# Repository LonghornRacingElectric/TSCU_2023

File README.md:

# TSCU_2023

The Tractiv System Control Unit (TSCU) controls the main logic of the Tractiv system (contactors, IMD, etc).

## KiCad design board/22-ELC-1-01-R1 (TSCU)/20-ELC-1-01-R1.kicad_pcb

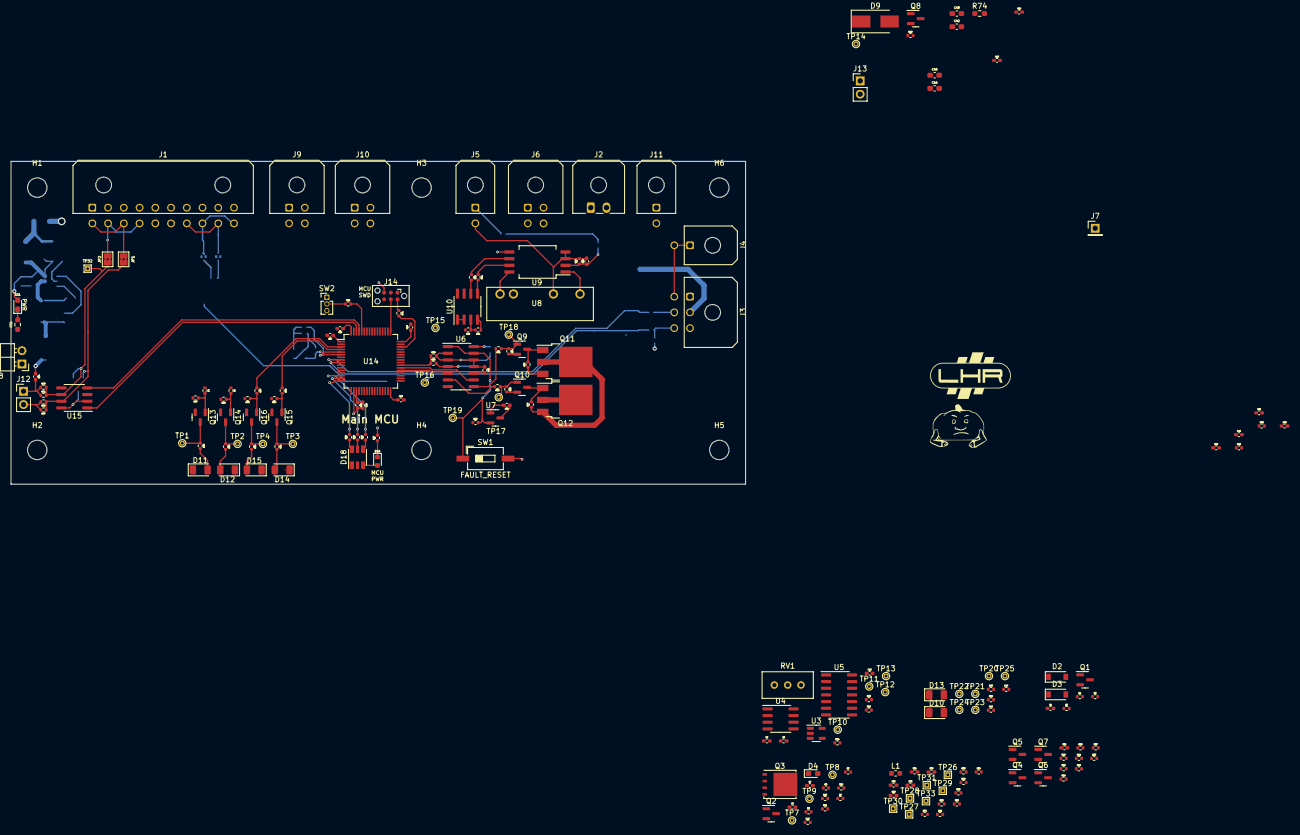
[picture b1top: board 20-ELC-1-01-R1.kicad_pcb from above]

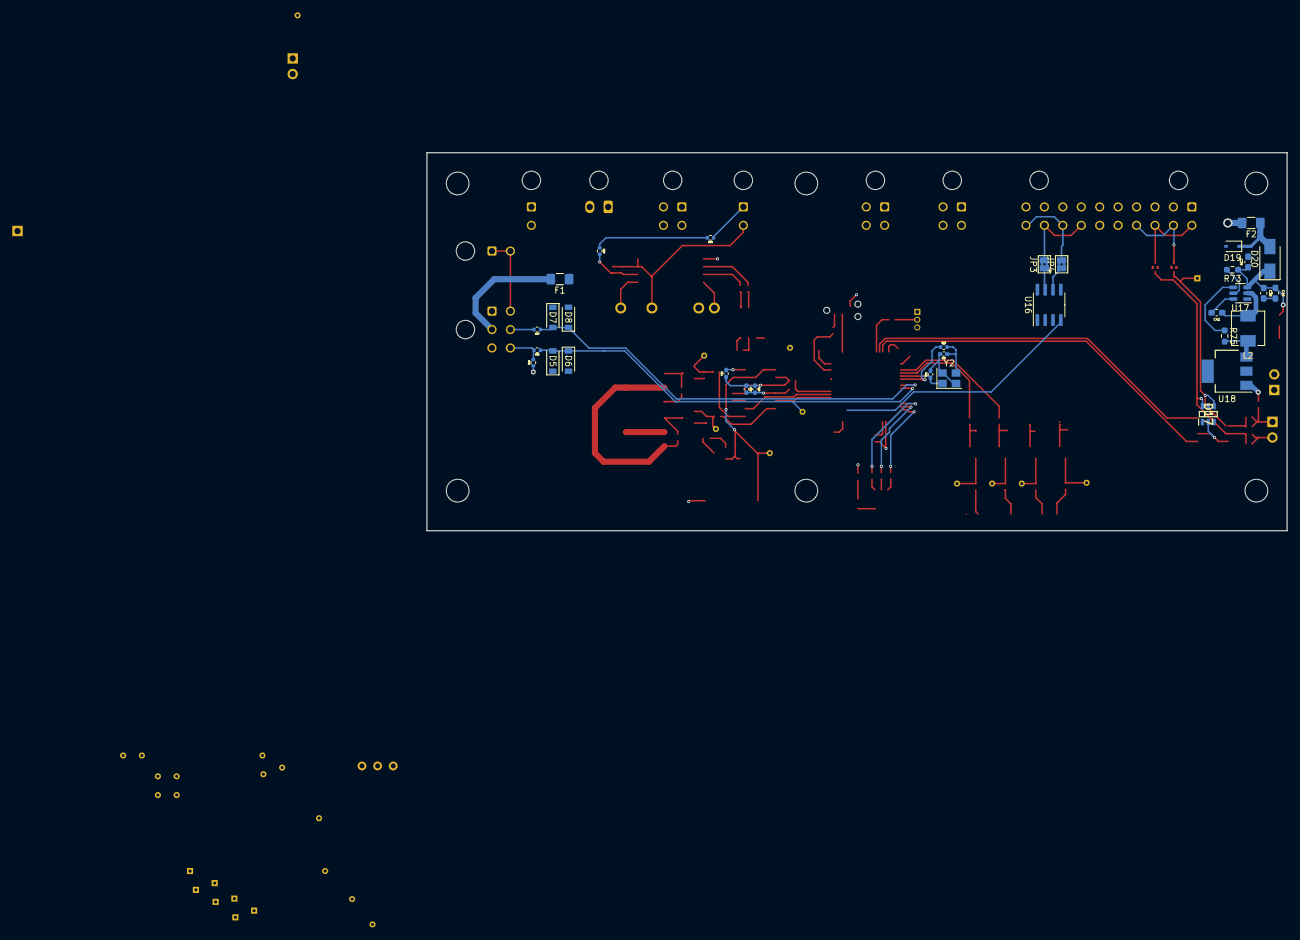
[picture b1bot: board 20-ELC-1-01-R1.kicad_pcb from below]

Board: 4 copper layers, 140.0 x 61.5 mm, 238 parts (33 on the bottom side), 130 nets.

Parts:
C1: 0.1uF; C_0402_1005Metric_Pad0.74x0.62mm_HandSolder_Reasonable_Text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
C6, C7, C9, C10, C11, C12, C13, C14, C15, C16, C17, C19, C20, C21, C22, C23: 0.1uf; C_0402_1005Metric_Pad0.74x0.62mm_HandSolder_Reasonable_Text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
C8: 47uf; C_0402_1005Metric_Pad0.74x0.62mm_HandSolder_Reasonable_Text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
C18: 1nf; C_0402_1005Metric_Pad0.74x0.62mm_HandSolder_Reasonable_Text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
C24: 4u7; C_0402_1005Metric_Pad0.74x0.62mm_HandSolder_Reasonable_Text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
C25, C26, C27, C28, C29: 100n; C_0402_1005Metric_Pad0.74x0.62mm_HandSolder_Reasonable_Text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
C30: 1u; C_0402_1005Metric_Pad0.74x0.62mm_HandSolder_Reasonable_Text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
C31: 10n; C_0402_1005Metric_Pad0.74x0.62mm_HandSolder_Reasonable_Text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
C32, C33: 0u1; C_0402_1005Metric_Pad0.74x0.62mm_HandSolder_Reasonable_Text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
C34, C35: 4.7n; C_0402_1005Metric_Pad0.74x0.62mm_HandSolder_Reasonable_Text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
C36, C37: 10p; C_0402_1005Metric_Pad0.74x0.62mm_HandSolder_Reasonable_Text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
C38, C39: 10uF; C_0603_1608Metric_Pad1.08x0.95mm_HandSolder_Reasonable_Text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
C40, C41: 100nF; C_0603_1608Metric_Pad1.08x0.95mm_HandSolder_Reasonable_Text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
C42, C43, C45: 22uF; C_0603_1608Metric_Pad1.08x0.95mm_HandSolder_Reasonable_Text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
C44: 1uF; C_0603_1608Metric_Pad1.08x0.95mm_HandSolder_Reasonable_Text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
D2, D3, D5, D6, D7, D8: B5819W; D_SOD-123
D4: LED_RED; LED_0603_1608Metric_Pad1.05x0.95mm_HandSolder
D9: P6SMB16CA; D_SMB_Handsoldering
D10: AMS_LED; LED_1206_3216Metric
D11: BMS_FAULT_LED; LED_1206_3216Metric
D12: IMS_FAULT_LED; LED_1206_3216Metric
D13: IMS_LED; LED_1206_3216Metric
D14: Precharge_CMD_LED; LED_1206_3216Metric
D15: Final_Close_Out_LED; LED_1206_3216Metric
D16: RED; LED_0603_1608Metric
D17: DT1446-04TS-7; SOT95P280X100-6N
D18: SMLVN6RGB; LED_ROHM_SMLVN6
D19: 32V; D_SOD-323
D20: 0.7dV; D_SMA
D21: LED; LED_0603_1608Metric_Pad1.05x0.95mm_HandSolder
F1, F2: 2A; Fuse_1206_3216Metric_Pad1.42x1.75mm_HandSolder
H1, H2, H3, H4, H5, H6: MountingHole; MountingHole_3.7mm
J1: Conn_01x20; Molex_Micro-Fit_3.0_43045-2000_2x10_P3.00mm_Horizontal
J2: Conn_01x02_Female; Molex_Micro-Fit_3.0_43650-0200_1x02_P3.00mm_Horizontal
J3: Conn_01x06; Molex_Micro-Fit_3.0_43045-0600_2x03_P3.00mm_Horizontal
J4, J5: Conn_01x02; Molex_Micro-Fit_3.0_43045-0200_2x01_P3.00mm_Horizontal
J6: Conn_01x06; Molex_Micro-Fit_3.0_43045-0400_2x02_P3.00mm_Horizontal
J7: Conn_01x01; PinHeader_1x01_P2.54mm_Vertical
J8: Conn_01x02; PinHeader_1x02_P2.54mm_Horizontal
J9, J10: Conn_02x02_Counter_Clockwise; Molex_Micro-Fit_3.0_43045-0400_2x02_P3.00mm_Horizontal
J11: Conn_01x01; Molex_Micro-Fit_3.0_43045-0200_2x01_P3.00mm_Horizontal
J12, J13: Conn_01x02; PinHeader_1x02_P2.54mm_Vertical
J14: SWD; Tag-Connect_TC2030-IDC-NL_2x03_P1.27mm_Vertical
JP1, JP2, JP3, JP4: SolderJumper-2_P1.3mm_Bridged2Bar_Pad1.0x1.5mm
L1: 68n; L_0603_1608Metric
L2: 4u7; L_Sunlord_MWSA0518_5.4x5.2mm
Q1, Q4, Q5, Q6, Q7, Q9, Q10, Q13, Q14, Q15, Q16: AO3400A; SOT-23
Q2: 2N7002; SOT-23
Q3: CSD18540Q5B; TDSON-8-1
Q8: Q_NMOS_DGS; SOT-23
Q11, Q12: SUD50P04-09L-E3; TO-252-3_TabPin2
R1, R3, R25, R29, R41, R42: 2.2k; R_0402_1005Metric
R2, R4, R5, R6, R8, R18, R19, R20, R26, R28, R30, R33, R76, R77: 10k; R_0402_1005Metric
R7, R57: 100; R_0402_1005Metric
R9, R13, R17, R27, R31, R32, R40: 1k; R_0402_1005Metric
R10, R11: 5.1k; R_0402_1005Metric
R12, R38, R39: 1M; R_0402_1005Metric
R14, R16, R21, R22, R23, R24, R34, R35, R36, R37, R47#2, R48#2, R78, R79: 100k; R_0402_1005Metric
R15: 120k; R_0402_1005Metric
R43, R44: 500; R_0402_1005Metric
R45, R46: 3.9k; R_0402_1005Metric
R47, R48, R49, R49#2, R50, R50#2, R51, R52, R58, R59, R60: 220; R_0402_1005Metric
R53, R54, R55, R56: 2k2; R_0402_1005Metric
R61, R62, R63, R64, R65, R66, R67, R68: 120; R_0402_1005Metric
R69: 47; R_0402_1005Metric
R70: 10K; R_0402_1005Metric
R71: 22; R_0402_1005Metric
R72: 470R; R_0603_1608Metric_Pad0.98x0.95mm_HandSolder
R73, R74: 10K; R_0603_1608Metric_Pad0.98x0.95mm_HandSolder
R75: 54.9K; R_0603_1608Metric_Pad0.98x0.95mm_HandSolder
RV1: R_POT_TRIM; Potentiometer_Bourns_3296W_Vertical
SW1: FAULT_RESET; SW_DIP_SPSTx01_Slide_6.7x4.1mm_W8.61mm_P2.54mm_LowProfile
SW2: SW_SPDT; PinHeader_1x03_P1.27mm_Vertical
TP1, TP2, TP3, TP4, TP7, TP8, TP9, TP10, TP11, TP12, TP13, TP14, TP15, TP16, TP17, TP18, TP19, TP20, TP21, TP22, TP23, TP24, TP25: TestPoint; TestPoint_THTPad_D1.0mm_Drill0.5mm
TP26, TP27, TP28, TP29, TP30, TP31, TP32, TP33: TestPoint_THTPad_1.0x1.0mm_Drill0.5mm
U3: 74AUC1G17; SOT-23-5
U4: LM393; SOIC-8_3.9x4.9mm_P1.27mm
U5: 74HC08_2AND; SOIC-14_3.9x8.7mm_P1.27mm
U6: 74HC74D,653; SOIC-14_3.9x8.7mm_P1.27mm
U7: SGM809-SXN3/TR; SOT-23
U8: RFMM-0505S
U9: ACPL-C79B; SSO-8_6.8x5.9mm_P1.27mm_Clearance8mm
U10: LM358; SOIC-8_3.9x4.9mm_P1.27mm
U14: STM32F105RCTx; LQFP-64_10x10mm_P0.5mm
U15, U16: SN65HVD230; SOIC-8_3.9x4.9mm_P1.27mm
U17: LMR51420; SOT-23-6
U18: AMS1117-3.3; SOT-223-3_TabPin2
X1: placeholder_for_picture; g_noidontwantthat
X2: placeholder_for_picture; logo_lhr
Y2: 16MHz; Crystal_SMD_3225-4Pin_3.2x2.5mm

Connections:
+3.3VA: C30.1, C31.1, L1.2, U14.13 (VDDA)
+3V3: C17.1, C24.1, C25.1, C26.1, C27.1, C28.1, C29.1, C32.1, C33.1, C45.1, D16.2 (A), D18.1 (BA), D18.2 (RA), D18.3 (GA), J14.1, L1.1, R53.1, R54.1, R55.1, R56.1, SW2.1 (A), U7.3 (VCC), U14.1 (VBAT), U14.19 (VDD), U14.32 (VDD), U14.48 (VDD), U14.64 (VDD), U15.3 (VCC), U16.3 (VCC), U18.2 (VO)
+5V: C6.2, C7.2, C9.1, C10.1, C14.2, C20.2, C23.1, C42.1, C43.1, C44.1, D2.1 (K), D5.1 (K), D7.1 (K), D17.5 (VCC), J8.1, L2.2, R1.1, R2.1, R8.1, R10.2, R11.2, R16.1, R33.1, R43.1, R75.2, RV1.1, U3.5 (VCC), U4.8 (V+), U5.14 (Vcc), U6.14 (VCC), U8.1 (VIN+), U9.8 (VDD2), U10.8 (V+), U18.3 (VI)
+24V: F1.1, F2.2, J1.2
/AMS_led: J1.8, Q4.3 (D)
/A_Vcar_sig: C21.1, R45.1, U10.7, U14.25 (PC5)
/BMS_Fault: R29.1, R30.1, TP15.1, U14.39 (PC8)
/BMS_fault_analog: C1.1, D2.2 (A), D3.1 (K), R3.1, U14.10 (PC2)
/CAN_H: J1.11, J1.13, JP1.2 (B)
/CAN_L: J1.12, J1.14, JP2.2 (B)
/Contactor Logic/Precharge_Active: R14.1, R15.1, TP10.1, U5.3 (1Y)
/D_AMS_Fault_Latched: R4.1, R18.1, U6.5 (Q), U14.37 (PC6)
/D_Aux_HS_sig: C7.1, J10.2, R11.1, TP8.1, U14.11 (PC3)
/D_Aux_LS_sig: C6.1, J9.2, R10.1, TP9.1, U5.2 (1B), U14.24 (PC4)
/D_Final_Close_Out: R13.1, R77.1, U5.6 (2Y), U14.3 (PC14)
/D_IMD_Fault_Latched: R5.1, R19.2, U6.9 (Q), U14.38 (PC7)
/D_Precharge_cmd: R28.2, R76.1, U5.1 (1A), U14.4 (PC15)
/D_Shutdown_Status_sig: R7.1, R8.2, R9.1, U14.40 (PC9)
/GLV Connections/DCDC_enable: J1.15, Q6.3 (D)
/HS_Con_GND: J6.2, Q3.1 (S), Q3.2 (S), Q3.3 (S), R12.2
/IMD_24V: F1.2, J3.2
/IMD_KE: J3.3, J3.4, J4.1, J4.2
/IMD_data: D7.2 (A), D8.1 (K), R27.1, U14.8 (PC0)
/IMD_data_low_side: J3.5, R27.2
/IMD_fault: C12.2, C15.2, D5.2 (A), D6.1 (K), R26.1, TP16.1, U6.10 (~S), U14.9 (PC1)
/IMD_led: J1.7, Q5.3 (D)
/IMD_status_output: J1.16, J3.6, R25.2, R26.2
/LS_Con_GND: J6.3, J9.3
/Microcontroller/BOOT0: R70.2, U14.60 (BOOT0)
/Microcontroller/CAN1_RX: TP28.1, U14.61 (PB8), U15.4 (R)
/Microcontroller/CAN1_TX: TP26.1, U14.62 (PB9), U15.1 (D)
/Microcontroller/CAN2_RX: TP29.1, U14.33 (PB12), U16.4 (R)
/Microcontroller/CAN2_TX: TP27.1, U14.34 (PB13), U16.1 (D)
/Microcontroller/HSE_in: C36.1, U14.5 (PD0), Y2.1
/Microcontroller/HSE_out: R69.1, U14.6 (PD1)
/Microcontroller/I2C1_SCL: R53.2, U14.58 (PB6)
/Microcontroller/I2C1_SDA: R54.2, U14.59 (PB7)
/Microcontroller/I2C2_SCL: R55.2, U14.29 (PB10)
/Microcontroller/I2C2_SDA: R56.2, U14.30 (PB11)
/Microcontroller/LED_B: R58.2, U14.16 (PA2)
/Microcontroller/LED_G: R59.2, U14.15 (PA1)
/Microcontroller/LED_R: R60.2, U14.14 (PA0)
/Microcontroller/SWCLK: J14.4, U14.49 (PA14)
/Microcontroller/SWDIO: R71.2, U14.46 (PA13)
/Orion_mpo_data_error: J2.2, Q1.1 (G), R1.2
/Power Supply 1/BUCK/EN: R73.2, U17.5 (EN)
/Power Supply 1/BUCK/SW: C41.1, L2.1, U17.2 (SW)
/Power Supply 1/BUCK/VBST: C41.2, U17.6 (VBST)
/Power Supply 1/BUCK/VFB: R74.1, R75.1, U17.4 (VFB)
/Power Supply 1/BUCK/V_in: C38.1, C39.1, C40.1, D20.1 (K), D21.2 (A), R73.1, U17.3 (VIN)
/Power Supply 1/DIODE: D19.1 (K), D20.2 (A), F2.1
/Precharge_Con_GND: J6.1, Q8.2 (S)
/Precharge_Timer: C8.1, R15.2, TP11.1, U3.2
/Shutdown Circuit Control/latch_ready: R33.2, SW1.1, TP19.1, U6.1 (~R), U6.13 (~R), U7.2 (~RESET)
/Telemetry_CAN_H: J1.17, J1.19, JP3.2 (B)
/Telemetry_CAN_L: J1.18, J1.20, JP4.2 (B)
/Voltage Measurement/HV+: J5.1, R38.1
/Voltage Measurement/iso_hv_0: C18.2, C19.1, J5.2, R40.2, U8.5 (VOUT-), U9.3 (IN-), U9.4 (GND1)
/Voltage Measurement/iso_hv_5: C19.2, U8.7 (VOUT+), U9.1 (VDD1)
/dcdc_enable: R20.2, U14.2 (PC13)
/shutdown_contactor: D9.1 (A1), J1.5, J9.4, J10.4, J11.1, R6.1, R17.2, TP7.1
/shutdown_in: J1.3, Q11.3 (S), R36.1
/shutdown_out: J1.4, Q12.2 (D)
/~dischage_disable: J1.6, Q7.3 (D)
GND: C1.2, C8.2, C9.2, C10.2, C11.2, C12.1, C13.1, C14.1, C15.1, C16.1, C17.2, C20.1, C22.1, C23.2, C24.2, C25.2, C26.2, C27.2, C28.2, C29.2, C30.2, C31.2, C32.2, C33.2, C34.1, C35.1, C36.2, C37.2, C38.2, C39.2, C40.2, C42.2, C43.2, C44.2, C45.2, D3.2 (A), D4.1 (K), D6.2 (A), D8.2 (A), D10.1 (K), D11.1 (K), D12.1 (K), D13.1 (K), D14.1 (K), D15.1 (K), D17.2 (VSS), D19.2 (A), J1.1, J2.1, J3.1, J7.1, J8.2, J9.1, J10.1, J14.5, Q1.2 (S), Q2.2 (S), Q4.2 (S), Q5.2 (S), Q6.2 (S), Q7.2 (S), Q9.2 (S), Q10.2 (S), Q13.2 (S), Q14.2 (S), Q15.2 (S), Q16.2 (S), R14.2, R21.2, R22.2, R23.2, R24.2, R25.1, R29.2, R34.2, R35.2, R44.2, R46.1, R47#2.2, R48#2.2, R57.2, R72.1, R74.2, R78.2, R79.2, RV1.3, SW1.2, SW2.3 (C), U3.3 (GND), U4.4 (V-), U5.7 (GND), U5.9 (3A), U5.10 (3B), U5.12 (4A), U5.13 (4B), U6.2 (D), U6.3 (C), U6.7 (GND), U6.11 (C), U6.12 (D), U7.1 (GND), U8.2 (VIN-), U9.5 (GND2), U10.4 (V-), U14.12 (VSSA), U14.18 (VSS), U14.31 (VSS), U14.47 (VSS), U14.63 (VSS), U15.2 (GND), U15.8 (Rs), U16.2 (GND), U16.8 (Rs), U17.1 (GND), U18.1 (GND), Y2.2, Y2.4
unnamed: C11.1, Q7.1 (G), R17.1, R24.1
unnamed: C13.2, C16.2, R30.2, U6.4 (~S)
unnamed: C18.1, R39.2, R40.1, U9.2 (IN+)
unnamed: C21.2, R42.2, R45.2, U10.6 (-)
unnamed: C22.2, R41.2, R46.2, U10.5 (+)
unnamed: C34.2, J12.1, R61.1, R63.1
unnamed: C35.2, J13.1, R62.1, R64.1
unnamed: C37.1, R69.2, Y2.3
unnamed: D4.2 (A), R9.2
unnamed: D9.2 (A2), J11.2, Q8.3 (D)
unnamed: D10.2 (A), R47.2
unnamed: D11.2 (A), R48.2, R49.2
unnamed: D12.2 (A), R49#2.2, R50.2
unnamed: D13.2 (A), R50#2.2
unnamed: D14.2 (A), R51.2
unnamed: D15.2 (A), R52.2
unnamed: D16.1 (K), R57.1
unnamed: D17.1 (I/O1), JP4.1 (A), R62.2, R64.2, TP33.1, U16.6 (CANL)
unnamed: D17.3 (I/O2), JP3.1 (A), R66.1, R68.1, TP31.1, U16.7 (CANH)
unnamed: D17.4 (I/O3), JP2.1 (A), R61.2, R63.2, TP32.1, U15.6 (CANL)
unnamed: D17.6 (I/O4), JP1.1 (A), R65.1, R67.1, TP30.1, U15.7 (CANH)
unnamed: D18.4 (GK), R60.1
unnamed: D18.5 (RK), R59.1
unnamed: D18.6 (BK), R58.1
unnamed: D21.1 (K), R72.2
unnamed: J10.3, Q3.5 (D)
unnamed: J12.2, R65.2, R67.2
unnamed: J13.2, R66.2, R68.2
unnamed: J14.2, R71.1
unnamed: Q1.3 (D), R2.2, R3.2
unnamed: Q2.1 (G), R6.2
unnamed: Q2.3 (D), R7.2
unnamed: Q3.4 (G), R12.1, R13.2
unnamed: Q4.1 (G), R18.2, R21.1
unnamed: Q5.1 (G), R19.1, R22.1
unnamed: Q6.1 (G), R20.1, R23.1
unnamed: Q8.1 (G), R28.1, TP14.1
unnamed: Q9.1 (G), R31.1, R34.1, TP18.1
unnamed: Q10.1 (G), R32.1, R35.1, TP17.1
unnamed: Q10.3 (D), Q12.1 (G), R37.2
unnamed: Q9.3 (D), Q11.1 (G), R36.2
unnamed: Q11.2 (D), Q12.3 (S), R37.1
unnamed: Q13.1 (G), R4.2, R47#2.1
unnamed: Q13.3 (D), R49.1, TP1.1
unnamed: Q14.1 (G), R5.2, R48#2.1
unnamed: Q14.3 (D), R50.1, TP2.1
unnamed: Q15.1 (G), R76.2, R78.1
unnamed: Q16.1 (G), R77.2, R79.1
unnamed: R16.2, TP13.1, U4.1, U5.4 (2A)
unnamed: R31.2, U6.8 (~Q)
unnamed: R32.2, U6.6 (~Q)
unnamed: R38.2, R39.1
unnamed: R41.1, U9.7 (OUT+)
unnamed: R42.1, U9.6 (OUT-)
unnamed: R43.2, R44.1, U10.3 (+)
unnamed: R47.1, TP20.1
unnamed: R48.1, TP21.1
unnamed: R49#2.1, TP22.1
unnamed: R50#2.1, TP23.1
unnamed: Q15.3 (D), R51.1, TP3.1, TP24.1
unnamed: Q16.3 (D), R52.1, TP4.1, TP25.1
unnamed: R70.1, SW2.2 (B)
unnamed: RV1.2, U4.2 (-)
unnamed: TP12.1, U3.4, U4.3 (+)
unnamed: U10.1, U10.2 (-)

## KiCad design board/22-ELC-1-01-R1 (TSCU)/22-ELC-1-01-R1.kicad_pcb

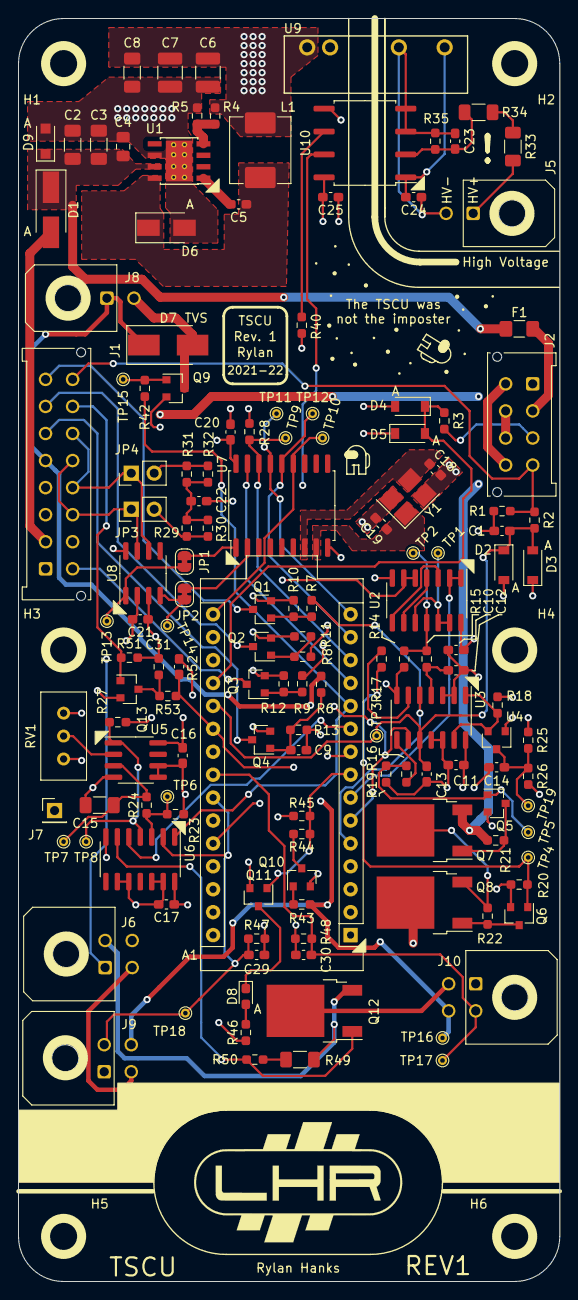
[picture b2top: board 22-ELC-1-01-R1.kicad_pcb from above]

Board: 4 copper layers, 60.0 x 140.0 mm, 150 parts (0 on the bottom side), 90 nets.

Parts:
A1: Arduino_Nano_v3.x; Arduino_Nano_Every
C1, C9, C10, C11, C12, C13, C14, C16, C17, C20, C21, C24, C25, C29, C30: 0.1uf; C_0603_1608Metric_Pad1.08x0.95mm_HandSolder
C2, C3, C8: 22uF; C_1206_3216Metric_Pad1.33x1.80mm_HandSolder
C4: 10uF; C_0805_2012Metric_Pad1.18x1.45mm_HandSolder
C5: 10nF; C_0603_1608Metric_Pad1.08x0.95mm_HandSolder
C6, C7: 100uF; C_1210_3225Metric_Pad1.33x2.70mm_HandSolder
C15: 68uf; C_1206_3216Metric_Pad1.33x1.80mm_HandSolder
C18, C19: 22pf; C_0603_1608Metric_Pad1.08x0.95mm_HandSolder
C22: 4.7nF; C_0603_1608Metric_Pad1.08x0.95mm_HandSolder
C23: 1nf; C_0603_1608Metric_Pad1.08x0.95mm_HandSolder
C31: 0.1uF; C_0603_1608Metric_Pad1.08x0.95mm_HandSolder
D1: SS54; D_SMA_Handsoldering
D2, D3, D4, D5: B5819W; D_SOD-123
D6: SS34; D_SMA
D7: P6SMB16CA; D_SMB_Handsoldering
D8: KT-0603R; LED_0603_1608Metric_Pad1.05x0.95mm_HandSolder
D9: D_SOD-123F
F1: 2A; Fuse_1206_3216Metric_Pad1.42x1.75mm_HandSolder
H1, H2, H3, H4, H5, H6: MountingHole; MountingHole_3.7mm
J1: Conn_01x116; Molex_Micro-Fit_3.0_43045-1612_2x08_P3.00mm_Vertical
J2: Conn_01x08; Molex_Micro-Fit_3.0_43045-0812_2x04_P3.00mm_Vertical
J5: Conn_01x02; Molex_Micro-Fit_3.0_43045-0200_2x01_P3.00mm_Horizontal
J6: Conn_01x06; Molex_Micro-Fit_3.0_43045-0400_2x02_P3.00mm_Horizontal
J7: Conn_01x01; PinHeader_1x01_P2.54mm_Vertical
J8: Conn_01x01; Molex_Micro-Fit_3.0_43045-0200_2x01_P3.00mm_Horizontal
J9, J10: Conn_02x02_Counter_Clockwise; Molex_Micro-Fit_3.0_43045-0400_2x02_P3.00mm_Horizontal
JP1, JP2: Jumper_2_Bridged; SolderJumper-2_P1.3mm_Bridged_RoundedPad1.0x1.5mm
JP3, JP4: NO_Jumper; PinHeader_1x02_P2.54mm_Vertical
L1: 15uH (4.5A); L_Abracon_ASPI-0630LR
Q1, Q2, Q3, Q4, Q5, Q6, Q11, Q13: AO3400A; SOT-23
Q7, Q8: IRFR5305TRPBF; TO-252-2
Q9: Q_NMOS_DGS; SOT-23
Q10: 2N7002; SOT-23
Q12: NCE3050K; TO-252-2
R1, R14, R51, R53: 2.2k; R_0603_1608Metric_Pad0.98x0.95mm_HandSolder
R2, R4, R7, R8, R9, R15, R18, R25, R42, R43, R45, R52: 10k; R_0603_1608Metric_Pad0.98x0.95mm_HandSolder
R3, R6, R16, R17, R35, R46, R50: 1k; R_0603_1608Metric_Pad0.98x0.95mm_HandSolder
R5: 3.24k; R_0603_1608Metric_Pad0.98x0.95mm_HandSolder
R10, R11, R12, R13, R19, R20, R21, R22, R23, R24, R27, R28: 100k; R_0603_1608Metric_Pad0.98x0.95mm_HandSolder
R26: 20k; R_0603_1608Metric_Pad0.98x0.95mm_HandSolder
R29, R30, R31, R32: 120; R_0603_1608Metric_Pad0.98x0.95mm_HandSolder
R33, R34, R49: 1M; R_1206_3216Metric_Pad1.30x1.75mm_HandSolder
R40: 3.9k; R_0603_1608Metric_Pad0.98x0.95mm_HandSolder
R44: 150; R_0603_1608Metric_Pad0.98x0.95mm_HandSolder
R47, R48: 5.1k; R_0603_1608Metric_Pad0.98x0.95mm_HandSolder
RV1: R_POT_TRIM; Potentiometer_Bourns_3296W_Vertical
TP1, TP2, TP3, TP4, TP5, TP6, TP7, TP8, TP9, TP10, TP11, TP12, TP13, TP14, TP15, TP16, TP17, TP18, TP19: TestPoint; TestPoint_THTPad_D1.0mm_Drill0.5mm
U1: TPS5430DDA; TI_SO-PowerPAD-8_ThermalVias
U2: 74HC00D,653; SOIC-14_3.9x8.7mm_P1.27mm
U3: 74HC74D,653; SOIC-14_3.9x8.7mm_P1.27mm
U4: SGM809-SXN3/TR; SOT-23
U5: LM393; SOIC-8_3.9x4.9mm_P1.27mm
U6: 74HC08_2AND; SOIC-14_3.9x8.7mm_P1.27mm
U7: MCP2515-xSO; SOIC-18W_7.5x11.6mm_P1.27mm
U8: SN65HVD230; SOIC-8_3.9x4.9mm_P1.27mm
U9: RFMM-0505S
U10: AMC1200BDUBR; SOP-8_6.62x9.15mm_P2.54mm
Y1: 16 MHz; Crystal_SMD_3225-4Pin_3.2x2.5mm_HandSoldering

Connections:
+5V: A1.27, C6.2, C7.2, C8.2, C10.2, C11.2, C16.1, C17.1, C20.2, C21.2, C25.2, C29.2, C30.2, D2.1, D4.1, L1.2, R4.1, R18.1, R25.1, R27.1, R28.1, R45.1, R46.1, R47.2, R48.2, R51.1, R52.1, RV1.1, U2.14, U3.14, U5.8, U6.14, U7.18, U8.3, U9.1, U10.8
+12V: C2.2, C3.2, C4.2, D1.1, D9.1, F1.1, U1.7
/12V_in: D1.2, J1.2
/AMS_led: J1.8, Q1.3
/A_Vcar_sig: A1.26, U10.7
/BMS_Fault: A1.7, U2.1, U2.2
/BMS_fault_analog: A1.21, C31.1, R53.1, U2.5, U2.6
/CAN/CAN_RX: JP2.2, U7.2
/CAN/CAN_TX: JP1.1, U7.1
/CAN_H: J1.11, J1.13, JP3.1, U8.7
/CAN_L: J1.12, J1.14, JP4.1, U8.6
/Contactor Logic/Precharge_Active: R23.1, R24.1, TP6.1, U6.3
/DCDC_enable_signal: J1.9, Q3.3
/D_AMS_Fault_Latched: A1.5, R7.1, U3.5
/D_Aux_HS_sig: A1.23, C30.1, J10.2, R48.1, TP17.1
/D_Aux_LS_sig: A1.24, C29.1, J9.2, R47.1, TP18.1, U6.2
/D_Final_Close_Out: Q12.1, R50.1, U6.6
/D_Final_Close_cmd: A1.10, U6.5
/D_IMD_Fault_Latched: A1.6, R8.2, U3.9
/D_Precharge_cmd: A1.11, R42.2, U6.1
/D_Shutdown_Status_sig: A1.8, Q11.1, R44.1, R45.2
/HS_Con_GND: J6.2, Q12.3, R49.2
/IMD_12V: F1.2, J2.2
/IMD_E: J2.6, J2.7
/IMD_KE: J2.5, J2.8
/IMD_data: A1.19, D4.2, D5.1, R3.1
/IMD_data_low_side: J2.3, R3.2
/IMD_fault: A1.20, C1.2, C13.2, D2.2, D3.1, R2.1, TP3.1, U3.10
/IMD_led: J1.7, Q2.3
/IMD_status_output: J1.16, J2.4, R1.2, R2.2
/LS_Con_GND: J6.3, J9.3
/Orion_mpo_data_error: J1.15, Q13.1, R51.2
/Precharge_Con_GND: J6.1, Q9.2
/Shutdown Circuit Control/3.3V: C14.1, R25.2, R26.1, TP19.1, U4.3
/Shutdown Circuit Control/latch_ready: R18.2, U3.1, U3.13, U4.2
/Shutdown Circuit Control/~BMS_Fault_AD: R14.1, R15.1, TP2.1, U2.11
/Voltage Measurement/HV+: J5.1, R33.1
/Voltage Measurement/HV-: C23.2, C24.1, J5.2, R35.2, U9.5, U10.3, U10.4
/Voltage Measurement/iso_hv_5: C24.2, U9.7, U10.1
/can_miso: A1.15, TP11.1, U7.15
/can_mosi: A1.14, TP12.1, U7.14
/can_sck: A1.16, TP10.1, U7.13
/can_~cs: A1.13, R28.2, TP9.1, U7.16
/can_~reset: A1.12, U7.17
/dcdc_enable: A1.9, R9.2
/shutdown_contactor: D7.1, J1.5, J8.1, J9.4, J10.4, R6.2, R43.1, TP16.1
/shutdown_in: J1.3, Q7.3, R21.1
/shutdown_out: J1.4, Q8.2
/~dischage_disable: J1.6, Q4.3
GND: A1.4, A1.29, C1.1, C2.1, C3.1, C4.1, C6.1, C7.1, C8.1, C9.2, C10.1, C11.1, C12.1, C13.1, C14.2, C15.2, C16.2, C17.2, C18.1, C19.2, C20.1, C21.1, C22.2, C25.1, C31.2, D3.2, D5.2, D6.2, D9.2, J1.1, J2.1, J7.1, J9.1, J10.1, Q1.2, Q2.2, Q3.2, Q4.2, Q5.2, Q6.2, Q10.2, Q11.2, Q13.2, R1.1, R5.2, R10.2, R11.2, R12.2, R13.2, R14.2, R19.2, R20.2, R23.2, R26.2, R40.1, RV1.3, U1.6, U1.9, U2.7, U3.2, U3.3, U3.7, U3.11, U3.12, U4.1, U5.4, U5.5, U5.6, U6.7, U6.9, U6.10, U6.12, U6.13, U7.9, U8.2, U8.8, U9.2, U10.5, Y1.2, Y1.4
unnamed: C5.1, D6.1, L1.1, U1.8
unnamed: C5.2, U1.1
unnamed: C9.1, Q4.1, R6.1, R13.1
unnamed: C12.2, R15.2, U3.4
unnamed: C15.1, R24.2, TP7.1, U5.3
unnamed: C18.2, U7.7, Y1.3
unnamed: C19.1, U7.8, Y1.1
unnamed: C22.1, R29.2, R30.2, R31.2, R32.2
unnamed: C23.1, R34.2, R35.1, U10.2
unnamed: D7.2, J8.2, Q9.3
unnamed: D8.1, Q11.3
unnamed: D8.2, R46.2
unnamed: J10.3, Q12.2
unnamed: JP1.2, TP13.1, U8.1
unnamed: JP2.1, TP14.1, U8.4
unnamed: JP3.2, R29.1, R30.1
unnamed: JP4.2, R31.1, R32.1
unnamed: Q1.1, R7.2, R10.1
unnamed: Q2.1, R8.1, R11.1
unnamed: Q3.1, R9.1, R12.1
unnamed: Q5.1, R16.1, R19.1, TP5.1
unnamed: Q5.3, Q7.1, R21.2
unnamed: Q6.1, R17.1, R20.1, TP4.1
unnamed: Q6.3, Q8.1, R22.2
unnamed: Q7.2, Q8.3, R22.1
unnamed: Q9.1, R42.1, TP15.1
unnamed: Q10.1, R43.2
unnamed: Q10.3, R44.2
unnamed: R49.1, R50.2
unnamed: Q13.3, R52.2, R53.2
unnamed: R4.2, R5.1, U1.4
unnamed: R16.2, U3.8
unnamed: R17.2, U3.6
unnamed: R27.2, TP8.1, U5.1, U6.4
unnamed: R33.2, R34.1
unnamed: R40.2, U10.6
unnamed: RV1.2, U5.2
unnamed: TP1.1, U2.10, U2.12, U2.13
unnamed: U2.3, U2.8
unnamed: U2.4, U2.9

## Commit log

2022-09-26 Added 2023KicadLibrary
2022-10-16 Initial commit - Board files
2022-10-16 Added FAULT_RESET button
2022-10-16 FAULT_RESET button cont'd
2022-10-30 Added few LEDs
2022-10-30 More work
2022-11-06 More LEDs and test points
2022-11-06 More LEDs and TPs
2022-11-06 Ready for review
2022-11-07 All good except need to switch everything to accepting 24v power
2022-12-04 Added standard VRM and more internal connections
2022-12-05 Finalized schematic, started board layout
2022-12-19 More progress
